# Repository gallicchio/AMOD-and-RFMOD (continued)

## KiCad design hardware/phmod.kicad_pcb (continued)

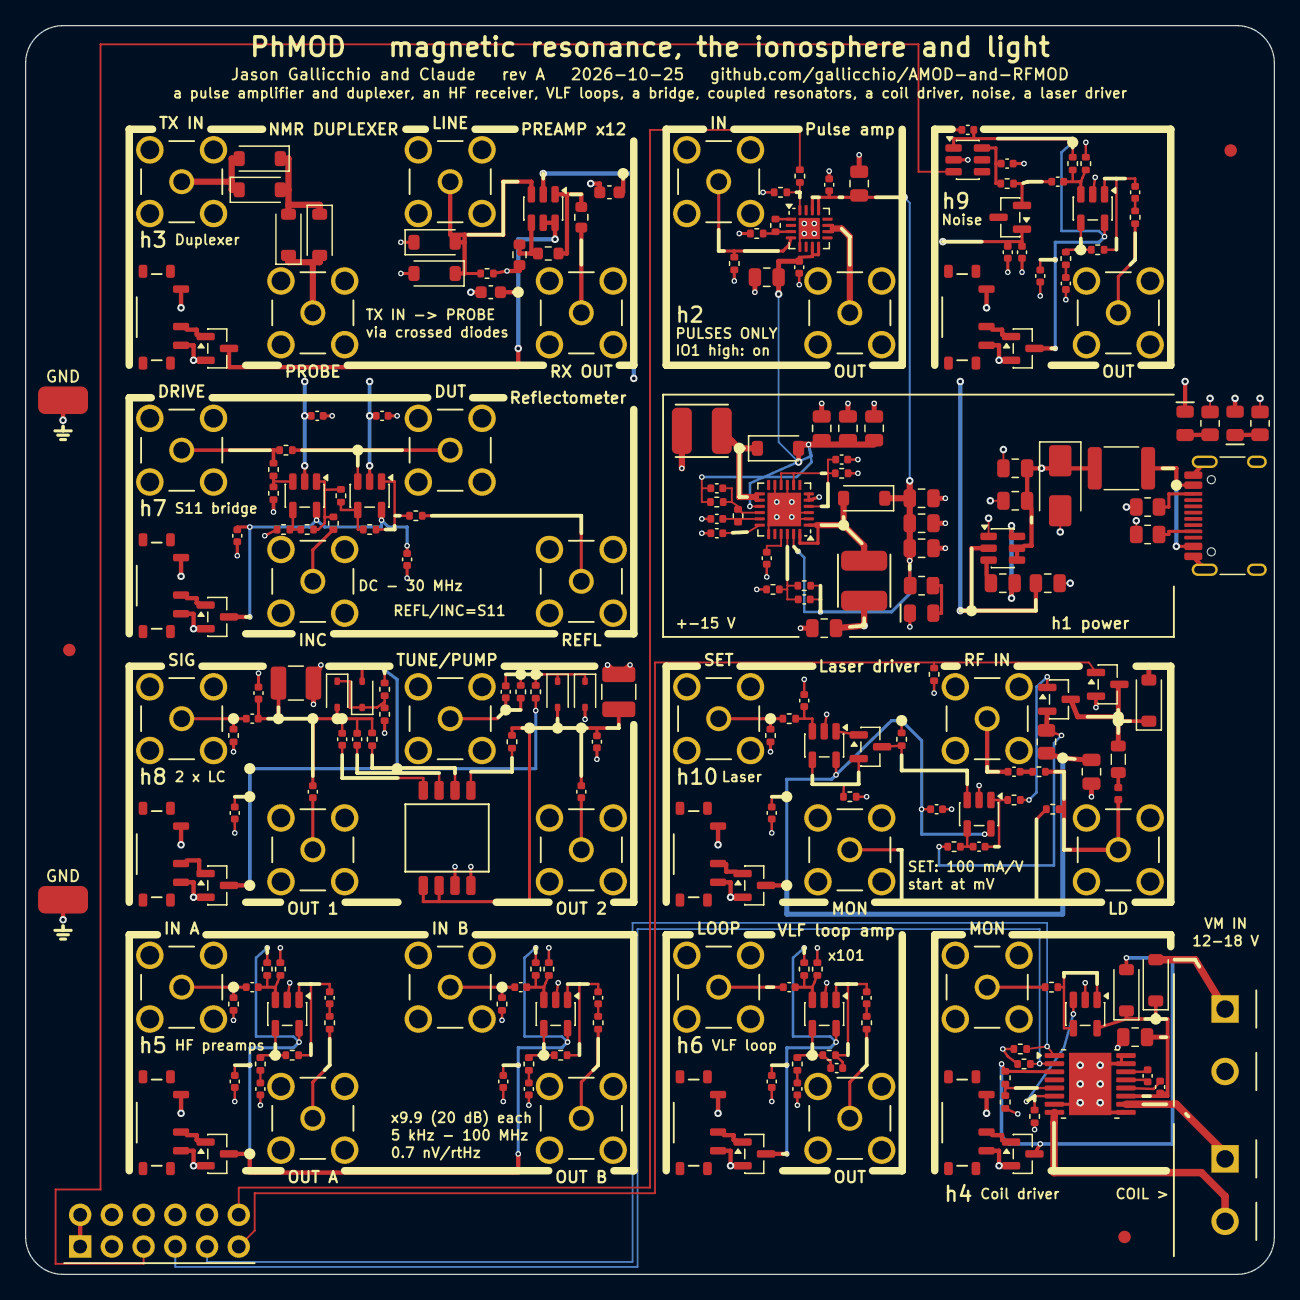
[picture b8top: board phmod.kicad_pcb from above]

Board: 4 copper layers, 100.0 x 100.0 mm, 234 parts (0 on the bottom side), 131 nets.

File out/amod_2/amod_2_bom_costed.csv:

Comment,Designator,Footprint,LCSC Part #,MPN,Qty,Unit $,Ext $,JLC
220n,C104,C_0402_1005Metric,C47129,CL05A224KA5NNNC,1,0.0083,0.008,extended
4.7n,C105,C_0402_1005Metric,C84705,CL05B472KB5NNNC,1,0.0044,0.004,extended
7.5p,C106,C_0402_1005Metric,C43514,0402CG7R5C500NT,1,0.0025,0.003,extended
4.7u,C108,C_0805_2012Metric,C1779,CL21A475KAQNNNE,1,0.0343,0.034,basic
22n,C402,C_0402_1005Metric,C337699,CL05B223KB5NNNC,1,0.0045,0.004,extended
4.7p,C802,C_0402_1005Metric,C1569,0402CG4R7C500NT,1,0.0058,0.006,extended
1p,C804,C_0402_1005Metric,C1550,0402CG1R0C500NT,1,0.0029,0.003,basic
1n,C806,C_0402_1005Metric,C1523,0402B102K500NT,1,0.0038,0.004,basic
6.8p,"C113,C807",C_0402_1005Metric,C1576,0402CG6R8C500NT,2,0.0026,0.005,extended
100n,"C301,C302",C_0603_1608Metric,C14663,CC0603KRX7R9BB104,2,0.0084,0.017,basic
10n,"C112,C1003",C_0402_1005Metric,C15195,CL05B103KB5NNNC,2,0.0039,0.008,basic
100p,"C603,C903,C1005",C_0402_1005Metric,C1546,0402CG101J500NT,3,0.0033,0.010,basic
2.2p,"C801,C803,C805,C808",C_0402_1005Metric,C1559,0402CG2R2C500NT,4,0.0037,0.015,extended
1u,"C501,C502,C503,C505,C506,C507,C601,C602,C604,C901,C905,C906,C907",C_0402_1005Metric,C14445,CL05A105KP5NNNC,13,0.0053,0.069,extended
10u,"C101,C102,C103,C109,C110,C111,C114,C115,C116,C117,C202,C204,C401,C1004",C_0805_2012Metric,C15850,CL21A106KAYNNNE,14,0.0426,0.596,basic
100n,"C107,C201,C203,C403,C504,C508,C605,C701,C702,C703,C704,C809,C902,C904,C908,C1001,C1002,C1006",C_0402_1005Metric,C1525,CL05B104KO5NNNC,18,0.0035,0.063,basic
SMAJ5.0A,D103,D_SMA,C78401,SMAJ5.0A,1,0.0537,0.054,extended
BB133,"D801,D802,D803,D804",D_SOD-323,C5334579,BB133,4,0.0604,0.242,extended
B5819W,"D101,D102,D401,D402,D1001",D_SOD-123,C64885,B5819W,5,0.0195,0.098,extended
1N4148W,"D301,D302,D303,D304,D305,D306",D_SOD-123,C81598,1N4148W,6,0.0124,0.074,basic
2A,F101,Fuse_1812_4532Metric,C210837,MF-MSMF200-2,1,0.0650,0.065,extended
USB-C,J101,USB_C_Receptacle_HRO_TYPE-C-31-M-12,C165948,TYPE-C-31-M-12,1,0.1888,0.189,extended
VM in,J402,TerminalBlock_KF301_1x02_P5.00mm,C474881,KF301-5.0-2P,1,0.1017,0.102,extended
coil,J403,TerminalBlock_KF301_1x02_P5.00mm,C474881,KF301-5.0-2P,1,0.1017,0.102,extended
Pmod,J505,PinHeader_2x06_P2.54mm_Horizontal_PZ254R-12-12P,C492434,PZ254R-12-12P,1,0.1036,0.104,extended
SMA,"J201,J202,J301,J302,J303,J304,J401,J501,J502,J503,J504,J601,J602,J701,J702,J703,J704,J801,J802,J803,J804,J901,J1001,J1002,J1003,J1004",SMA_BWSMA-KE-Z001_Vertical,C496549,BWSMA-KE-Z001,26,0.4043,10.512,extended
330n,L1001,L_0805_2012Metric,C98210,SDWL2012CR33JSTF,1,0.0851,0.085,extended
27n,L1002,L_0402_1005Metric,C882469,LQW15AN27NG80D,1,0.0902,0.090,extended
+15V,LED101,LED_0805_2012Metric_Kbar,C2296,KT-0805Y,1,0.0146,0.015,basic
-5V,LED102,LED_0805_2012Metric_Kbar,C84256,NCD0805R1,1,0.0135,0.013,basic
+5V,LED103,LED_0805_2012Metric_Kbar,C2297,KT-0805G,1,0.0164,0.016,basic
4.7u,"L101,L102",L_4x4_XRNR4030,C57269,SWPA4030S4R7MT,2,0.0603,0.121,extended
10u,"L801,L802",L_1210_3225Metric,C76835,NLV32T-100J-PF,2,0.0578,0.116,extended
MMBT3904,Q902,SOT-23,C20526,MMBT3904(RANGE:100-300),1,0.0116,0.012,basic
2N7002,Q1002,SOT-23,C8545,2N7002,1,0.0161,0.016,basic
AO3400A,Q1004,SOT-23,C20917,AO3400A,1,0.0889,0.089,basic
AO3401A,"Q301,Q401,Q501,Q601,Q701,Q801,Q901,Q1001,Q1003",SOT-23,C15127,AO3401A,9,0.0959,0.863,basic
105k,R101,R_0402_1005Metric,C25742,0402WGF1053TCE,1,0.0021,0.002,extended
1.3M,R102,R_0402_1005Metric,C423245,0402WGF1304TCE,1,0.0005,0.001,extended
88.7k,R104,R_0402_1005Metric,C25922,0402WGF8872TCE,1,0.0016,0.002,extended
1M,R105,R_0402_1005Metric,C26083,0402WGF1004TCE,1,0.0015,0.002,basic
4.7k,R106,R_0805_2012Metric,C17673,0805W8F4701T5E,1,0.0051,0.005,basic
698,R201,R_0402_1005Metric,C33359,0402WGF6980TCE,1,0.0010,0.001,extended
75,R202,R_0402_1005Metric,C25133,0402WGF750JTCE,1,0.0013,0.001,extended
4.7k,R205,R_0402_1005Metric,C25900,0402WGF4701TCE,1,0.0021,0.002,basic
1.1k,R302,R_0603_1608Metric,C22764,0603WAF1101T5E,1,0.0018,0.002,extended
49.9,R303,R_0603_1608Metric,C23185,0603WAF499JT5E,1,0.0021,0.002,basic
100R,R304,R_0603_1608Metric,C22775,0603WAF1000T5E,1,0.0023,0.002,basic
5.1k,R403,R_0402_1005Metric,C25905,0402WGF5101TCE,1,0.0023,0.002,basic
3.3k,R404,R_0402_1005Metric,C25890,0402WGF3301TCE,1,0.0036,0.004,basic
1.5k,R405,R_0402_1005Metric,C25867,0402WGF1501TCE,1,0.0029,0.003,basic
680,R901,R_0402_1005Metric,C25130,0402WGF6800TCE,1,0.0012,0.001,basic
10,R1007,R_0805_2012Metric,C17415,0805W8F100JT5E,1,0.0040,0.004,basic
47,R1008,R_0402_1005Metric,C25118,0402WGF470JTCE,1,0.0012,0.001,basic
5.1k,"R107,R108",R_0805_2012Metric,C27834,0805W8F5101T5E,2,0.0036,0.007,basic
1k,"R109,R110",R_0805_2012Metric,C17513,0805W8F1001T5E,2,0.0035,0.007,basic
2k,"R804,R807",R_0402_1005Metric,C4109,0402WGF2001TCE,2,0.0026,0.005,basic
240,"R504,R510,R904",R_0402_1005Metric,C25094,0402WGF2400TCE,3,0.0016,0.005,extended
27,"R505,R511,R905",R_0402_1005Metric,C25100,0402WGF270JTCE,3,0.0013,0.004,extended
100,"R103,R604,R1005",R_0402_1005Metric,C25076,0402WGF1000TCE,3,0.0012,0.004,basic
499,"R704,R705,R707,R708",R_0402_1005Metric,C4125,0402WGF4990TCE,4,0.0010,0.004,basic
1k,"R1002,R1003,R1004,R1006",R_0402_1005Metric,C11702,0402WGF1001TCE,4,0.0013,0.005,basic
10k,"R204,R502,R503,R508,R509,R603,R902,R903,R1009",R_0402_1005Metric,C25744,0402WGF1002TCE,9,0.0011,0.010,basic
100k,"R401,R402,R601,R602,R802,R803,R805,R806,R1010",R_0402_1005Metric,C25741,0402WGF1003TCE,9,0.0015,0.013,basic
49.9,"R203,R301,R406,R501,R506,R507,R512,R605,R701,R702,R703,R706,R709,R801,R906,R1001",R_0402_1005Metric,C25120,0402WGF499JTCE,16,0.0016,0.026,basic
DIP4,SW802,SW_DIP_SPSTx04_Slide_1.27mm_DSHP04,C40736,DSHP04TSGET,1,0.5450,0.545,extended
ON,"SW301,SW401,SW501,SW601,SW701,SW801,SW901,SW1001",SW_SPDT_Shouhan_MSK12C02,C431540,MSK12C02,8,0.0529,0.423,extended
GND,"TP9901,TP9902",TestPoint_Loop_RH-5019,C5199800,RH-5019,2,0.0966,0.193,extended
TPS65131,U101,QFN-24-1EP_4x4mm_P0.5mm_EP2.7x2.7mm,C87663,TPS65131RGER,1,2.8786,2.879,extended
LM2664,U102,SOT-23-6,C108573,LM2664M6X/NOPB,1,0.3346,0.335,extended
THS3491,U201,QFN-16-1EP_3x3mm_P0.5mm_EP1.7x1.7mm,C2058688,THS3491IRGTR,1,13.5355,13.536,extended
OPA847,U301,SOT-23-6,C160422,OPA847IDBVR,1,10.3296,10.330,extended
DRV8876,U401,HTSSOP-16-1EP_4.4x5mm_P0.65mm_EP3.4x5mm_Mask2.66x2.46mm,C575551,DRV8876PWPR,1,0.6612,0.661,extended
TPS22917,U901,SOT-23-6,C2681320,TPS22917DBVR,1,0.3653,0.365,extended
LMH6629,"U501,U502,U902",SOT-23-5,C2059678,LMH6629MFX/NOPB,3,5.4577,16.373,extended
OPA810,"U402,U601,U701,U702,U1001,U1002",SOT-23-5,C2833513,OPA810IDBVR,6,3.0996,18.598,extended

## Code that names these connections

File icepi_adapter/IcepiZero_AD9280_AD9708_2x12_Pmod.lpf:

# IcepiZero_AD9280_AD9708_2x12_Pmod
# HS-AD/DA V2.0 AD9280 ADC + AD9708 DAC, plus a Pmod
# GENERATED by make_boards.py from the same pin assignment as
# the PCB -- do not edit.  Rebuild with:
#     KICAD=10 ./kicad-python.sh make_boards.py

# ---- the converter module, through this adapter -------------
LOCATE COMP "ad0" SITE "R1";   # AD0, header pin 7 / GPIO4
IOBUF  PORT "ad0" IO_TYPE=LVCMOS33 PULLMODE=NONE DRIVE=4 SLEWRATE=SLOW;
LOCATE COMP "ad1" SITE "R3";   # AD1, header pin 11 / GPIO17
IOBUF  PORT "ad1" IO_TYPE=LVCMOS33 PULLMODE=NONE DRIVE=4 SLEWRATE=SLOW;
LOCATE COMP "ad2" SITE "N4";   # AD2, header pin 12 / GPIO18
IOBUF  PORT "ad2" IO_TYPE=LVCMOS33 PULLMODE=NONE DRIVE=4 SLEWRATE=SLOW;
LOCATE COMP "ad3" SITE "P3";   # AD3, header pin 13 / GPIO27
IOBUF  PORT "ad3" IO_TYPE=LVCMOS33 PULLMODE=NONE DRIVE=4 SLEWRATE=SLOW;
LOCATE COMP "ad4" SITE "P2";   # AD4, header pin 15 / GPIO22
IOBUF  PORT "ad4" IO_TYPE=LVCMOS33 PULLMODE=NONE DRIVE=4 SLEWRATE=SLOW;
LOCATE COMP "ad5" SITE "M2";   # AD5, header pin 16 / GPIO23
IOBUF  PORT "ad5" IO_TYPE=LVCMOS33 PULLMODE=NONE DRIVE=4 SLEWRATE=SLOW;
LOCATE COMP "ad6" SITE "L1";   # AD6, header pin 18 / GPIO24
IOBUF  PORT "ad6" IO_TYPE=LVCMOS33 PULLMODE=NONE DRIVE=4 SLEWRATE=SLOW;
LOCATE COMP "ad7" SITE "L2";   # AD7, header pin 19 / GPIO10
IOBUF  PORT "ad7" IO_TYPE=LVCMOS33 PULLMODE=NONE DRIVE=4 SLEWRATE=SLOW;
LOCATE COMP "aclk" SITE "J1";   # ACLK, header pin 21 / GPIO9
IOBUF  PORT "aclk" IO_TYPE=LVCMOS33 PULLMODE=NONE DRIVE=4 SLEWRATE=SLOW;
LOCATE COMP "dclk" SITE "G2";   # DCLK, header pin 23 / GPIO11
IOBUF  PORT "dclk" IO_TYPE=LVCMOS33 PULLMODE=NONE DRIVE=4 SLEWRATE=SLOW;
LOCATE COMP "da7" SITE "H2";   # DA7, header pin 24 / GPIO8
IOBUF  PORT "da7" IO_TYPE=LVCMOS33 PULLMODE=NONE DRIVE=4 SLEWRATE=SLOW;
LOCATE COMP "da6" SITE "G1";   # DA6, header pin 26 / GPIO7
IOBUF  PORT "da6" IO_TYPE=LVCMOS33 PULLMODE=NONE DRIVE=4 SLEWRATE=SLOW;
LOCATE COMP "da5" SITE "E1";   # DA5, header pin 29 / GPIO5
IOBUF  PORT "da5" IO_TYPE=LVCMOS33 PULLMODE=NONE DRIVE=4 SLEWRATE=SLOW;
LOCATE COMP "da4" SITE "F3";   # DA4, header pin 31 / GPIO6
IOBUF  PORT "da4" IO_TYPE=LVCMOS33 PULLMODE=NONE DRIVE=4 SLEWRATE=SLOW;
LOCATE COMP "da3" SITE "J3";   # DA3, header pin 32 / GPIO12
IOBUF  PORT "da3" IO_TYPE=LVCMOS33 PULLMODE=NONE DRIVE=4 SLEWRATE=SLOW;
LOCATE COMP "da2" SITE "E3";   # DA2, header pin 33 / GPIO13
IOBUF  PORT "da2" IO_TYPE=LVCMOS33 PULLMODE=NONE DRIVE=4 SLEWRATE=SLOW;
LOCATE COMP "da1" SITE "E4";   # DA1, header pin 35 / GPIO19
IOBUF  PORT "da1" IO_TYPE=LVCMOS33 PULLMODE=NONE DRIVE=4 SLEWRATE=SLOW;
LOCATE COMP "da0" SITE "D4";   # DA0, header pin 37 / GPIO26
IOBUF  PORT "da0" IO_TYPE=LVCMOS33 PULLMODE=NONE DRIVE=4 SLEWRATE=SLOW;

# ---- the Pmod socket J3: pmod[n-1] is the Pmod standard's IOn (pins 1-4, 7-10) -----
# ---- J3 layout: spec (make_boards.py PMOD_LAYOUT) -----
LOCATE COMP "pmod[0]" SITE "F2";   # PMOD1, socket pad 11, header pin 40 / GPIO21
IOBUF  PORT "pmod[0]" IO_TYPE=LVCMOS33 PULLMODE=NONE DRIVE=4 SLEWRATE=SLOW;
LOCATE COMP "pmod[1]" SITE "H3";   # PMOD2, socket pad 9, header pin 36 / GPIO16
IOBUF  PORT "pmod[1]" IO_TYPE=LVCMOS33 PULLMODE=NONE DRIVE=4 SLEWRATE=SLOW;
LOCATE COMP "pmod[2]" SITE "G3";   # PMOD3, socket pad 7, header pin 27 / GPIO0
IOBUF  PORT "pmod[2]" IO_TYPE=LVCMOS33 PULLMODE=NONE DRIVE=4 SLEWRATE=SLOW;
LOCATE COMP "pmod[3]" SITE "N1";   # PMOD4, socket pad 5, header pin 10 / GPIO15
IOBUF  PORT "pmod[3]" IO_TYPE=LVCMOS33 PULLMODE=NONE DRIVE=4 SLEWRATE=SLOW;
LOCATE COMP "pmod[4]" SITE "F1";   # PMOD5, socket pad 12, header pin 38 / GPIO20
IOBUF  PORT "pmod[4]" IO_TYPE=LVCMOS33 PULLMODE=NONE DRIVE=4 SLEWRATE=SLOW;
LOCATE COMP "pmod[5]" SITE "K3";   # PMOD6, socket pad 10, header pin 28 / GPIO1
IOBUF  PORT "pmod[5]" IO_TYPE=LVCMOS33 PULLMODE=NONE DRIVE=4 SLEWRATE=SLOW;
LOCATE COMP "pmod[6]" SITE "J2";   # PMOD7, socket pad 8, header pin 22 / GPIO25
IOBUF  PORT "pmod[6]" IO_TYPE=LVCMOS33 PULLMODE=NONE DRIVE=4 SLEWRATE=SLOW;
LOCATE COMP "pmod[7]" SITE "P1";   # PMOD8, socket pad 6, header pin 8 / GPIO14
IOBUF  PORT "pmod[7]" IO_TYPE=LVCMOS33 PULLMODE=NONE DRIVE=4 SLEWRATE=SLOW;

# ---- the Icepi Zero itself ----------------------------
LOCATE COMP "clk50" SITE "M1";   # 50 MHz oscillator -- the only clock on the board
IOBUF  PORT "clk50" IO_TYPE=LVCMOS33 PULLMODE=NONE;
LOCATE COMP "uart_tx" SITE "K15";   # to U9 (FT231X) RXD -> /dev/ttyUSB* on the host
IOBUF  PORT "uart_tx" IO_TYPE=LVCMOS33 PULLMODE=NONE;
LOCATE COMP "uart_rx" SITE "K16";   # from U9 (FT231X) TXD
IOBUF  PORT "uart_rx" IO_TYPE=LVCMOS33 PULLMODE=NONE;
LOCATE COMP "led0" SITE "E13";
IOBUF  PORT "led0" IO_TYPE=LVCMOS33 PULLMODE=NONE;
LOCATE COMP "led1" SITE "D14";
IOBUF  PORT "led1" IO_TYPE=LVCMOS33 PULLMODE=NONE;
LOCATE COMP "led2" SITE "E12";
IOBUF  PORT "led2" IO_TYPE=LVCMOS33 PULLMODE=NONE;
LOCATE COMP "led3" SITE "C13";
IOBUF  PORT "led3" IO_TYPE=LVCMOS33 PULLMODE=NONE;
LOCATE COMP "led4" SITE "D13";
IOBUF  PORT "led4" IO_TYPE=LVCMOS33 PULLMODE=NONE;
LOCATE COMP "btn0" SITE "C4";   # also the LiteX reset button
IOBUF  PORT "btn0" IO_TYPE=LVCMOS33 PULLMODE=UP;
LOCATE COMP "btn1" SITE "C5";
IOBUF  PORT "btn1" IO_TYPE=LVCMOS33 PULLMODE=UP;

# The oscillator, so nextpnr reports the real timing margin
# instead of guessing.
FREQUENCY PORT "clk50" 50 MHZ;

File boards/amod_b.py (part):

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    t.pwr_flags = [VMB]
    t.jack("BR", "I", "IJ", "out", "", silk="I 1V/A")
    bx = BUS_X - t.x0
    rsh = t.add("R", "R1206 0.1R", "0.1", 3.0, 3.25, 0, {"1": VM, "2": VMB}, label=None)
    t.via(VM, bx, BUS_END - t.y0)
    t.wire(VM, [(bx, BUS_END - t.y0), (rsh, "1")], width=WP)
    # VMB: a via beside the shunt, the back left to the gutter and down it to the driver
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    # slots to the left (to b7).  VDD's via is on the +3.3 V strip (the gutter between rows 1 and 2 runs under the middle)
    enc = t.add("U", "MT6701", "MT6701", cx, cy, 180, {"1": "+3V3", "3": "/ANG", "4": "GND", "6": "/ENC_DO", "7": "/PMOD4", "8": "/PMOD6"},
                hide_value=True, label=None)
    for net, pin, y in (("/ENC_DO", "6", cy - 0.635), ("/PMOD4", "7", cy + 0.635), ("/PMOD6", "8", cy + 1.905)):
        t.via(net, *ENC_VIA[net], fine=True)
        t.wire(net, [(enc, pin), ENC_VIA[net]], width=0.2)
    t.via("/ANG", *ENC_VIA["/ANG"], fine=True)
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    # the index sensor under the rim toward b9: its LED from +5 V through 180 ohm; collector and emitter on vias for b9
    a = math.radians(-60.0)
    qx, qy = cx + GIMBAL_R_INDEX * math.cos(a), cy + GIMBAL_R_INDEX * math.sin(a)
    q = t.add("U", "QRE1113GR", "QRE1113", qx, qy, 0, {"1": "QLA", "2": "GND", "3": "/IDX_C", "4": "/IDX_E"}, hide_value=True, label=None)
    rq = t.add("R", "R0805 180R", "180", qx - 0.9, qy - 4.86, 0, {"1": "+5V", "2": "QLA"}, label=None)
    t.wire("QLA", [(rq, "2"), (qx, qy - 3.6), (qx - 0.9, qy - 2.83), (q, "1")], width=W)
    t.via("+5V", qx - 3.0, qy - 4.86)
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    t.via(VMB, bx, 10.6)
    t.wire(VMB, [(drv, "8"), (23.2, Y + 0.67), (23.8, 10.27), (23.8, 10.6)], width=0.25)
    t.wire(VMB, [(23.8, 10.6), (bx, 10.6)], width=1.0)
    cvm = t.add("C", "C0402 100nF", "100n", 25.2, 12.0, 90, {"1": "GND", "2": VMB}, label=None)            # pad 2 up
    t.wire(VMB, [(cvm, "2"), (25.2, 10.9)], width=0.4)
    t.gnd_stub(cvm, "1", (26.2, 12.8), sym=(0, 0), width=W)
    cbk = t.add("C", "C0805 10uF", "10u", 28.4, 13.0, 0, {"1": "GND", "2": VMB}, label=None)
    t.wire(VMB, [(cbk, "2"), (29.35, 10.9)], width=0.6)
    t.gnd_stub(cbk, "1", (27.45, 14.4), sym=(0, 0), width=W)
    ccp = t.add("C", "C0402 100nF", "100n", 23.0, 11.9, 0, {"1": "CP", "2": VMB}, label=None)
    t.wire("CP", [(drv, "6"), (X + 0.8, 11.2), (ccp, "1")], width=F)
    t.wire(VMB, [(ccp, "2"), (23.8, 11.3), (23.8, 10.6)], width=0.25)
    # ---- EN: the three INL pins joined over the driver's top-left corner, from the comparator
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    low side only, sampled) it shows what a low-side amplifier misses."""
    t = Tile("b11", "phase current", [(3, 3)], supply="+-5 V", subtitle="INA240", sections=["Motors"])
    t.jack("BR", "IPA", "IJ", "out", "", silk="IPA 1V/A")
    rsh = t.add("R", "R1206 0.05R", "0.05", 3.6, 8.87, 0, {"1": "/PHA", "2": "/PHAM"}, label=None)
    t.wire("/PHA", [(-0.75, 8.87), (rsh, "1")], width=0.6)
    # the return to the terminal's pin 3, up and left along y 4.35
    t.wire("/PHAM", [(rsh, "2"), (5.6, 7.6), (5.6, 4.35), (-4.8, 4.35)], width=0.6)
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    t.fine = True
    F = 0.15
    imu = t.add("U", "LSM6DSO", "LSM6DSO", 10.5, 15.0, 270, {"1": "/PMOD3", "2": "GND", "3": "GND", "5": "+3V3", "6": "GND", "7": "GND", "8": "+3V3",
                                                             "12": "/PMOD8", "13": "/PMOD4", "14": "/PMOD7"}, hide_value=False, label=None)
    # SPI: the right side's three to vias staggered so the lanes on the back pass between them; MISO's from the top
    for net, pad, mid, via in (("/PMOD7", "14", [], (12.45, 14.5)), ("/PMOD8", "12", [], B6_VIA["/PMOD8"]), ("/PMOD4", "13", [], B6_VIA["/PMOD4"]),
                               ("/PMOD3", "1", [(11.25, 13.5)], (12.45, 13.5))):
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    through 49.9 ohm.  A white mark on the bell's rim gives a pulse once a turn: an index for the encoder, a tachometer."""
    t = Tile("b9", "index", [(2, 0)], supply="+-5 V", subtitle="QRE1113", sections=["Motors"])
    t.jack("BR", "IDX", "XJ", "out", "")
    ud = t.add("U", "OPA810", "OPA810", 10.6, 9.0, 0, {"1": "XO", "2": "-5V", "3": "GND", "4": "/IDX_C", "5": "+5V"}, hide_value=False, label=None)
    rf = t.add("R", "R0402 4.7k", "4.7k", 10.6, 12.0, 0, {"1": "/IDX_C", "2": "XO"}, label=None)
    cf = t.add("C", "C0402 100pF", "100p", 10.6, 13.2, 0, {"1": "/IDX_C", "2": "XO"}, label=None)
    re = t.add("R", "R0402 100R", "100", 6.0, 16.4, 0, {"1": "/IDX_E", "2": "-5V"}, label=None)
    ro = t.add("R", "R0402 49.9R", "49.9", 15.25, 10.6, 90, {"1": "XJ", "2": "XO"}, label=None)
    for (net, a, b) in (("/IDX_C", (rf, "1"), (ud, "4")), ("/IDX_C", (cf, "1"), (rf, "1")), ("XO", (rf, "2"), (ud, "1")), ("XO", (cf, "2"), (rf, "2")),
                        ("XO", (ro, "2"), (ud, "1"))):
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
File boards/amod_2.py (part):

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    t.wire("-15V", [(cn2, "2"), (9.55, 13.75)], width=0.4)
    # PD: 4.7 k from Pmod IO1 (along the top from the gutter on the left), 10 k to ground
    rpd = t.add("R", "R0402 10k", "10k", 9.7, 5.6, 0, {"1": "GND", "2": "PD"}, label=None)
    rs = t.add("R", "R0402 4.7k", "4.7k", 11.25, 4.3, 90, {"1": "PD", "2": "/PMOD1"}, label=None)              # pad 1 down
    t.wire("PD", [(u, "16"), (11.25, 5.6), (rpd, "2")], width=F)
    t.wire("PD", [(11.25, 5.6), (rs, "1")], width=F)
    gnd(t, rpd, "1", (8.3, 5.6), w=0.2)
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    used = PMOD_USED                                       # the lines some tile uses; the others stay open on the plug
    pads = {"12": "/PMOD1", "10": "/PMOD2", "8": "/PMOD3", "6": "/PMOD4", "11": "/PMOD5", "9": "/PMOD6", "7": "/PMOD7", "5": "/PMOD8"}
    pins = {k: v for k, v in pads.items() if v in used}
    pins.update({"3": "GND", "4": "GND", "1": "/PMOD_VCC", "2": "/PMOD_VCC"})
    pm = t.add("J", "PMOD", "Pmod", 2.97, 24.25, 0, pins, hide_value=True)
    t.wire("/PMOD_VCC", [(pm, "1"), (pm, "2")], silk=False)
    t.text(1.2, 9.4, "Y5", 1.2, 0.2, "left")
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    power_header(t, rail="+5V")
    t.wire("VS", [HDR_VS, (10.2, 18.1)], width=0.35)
    # the switch: TPS22917 (rot 0: VIN 1, GND 2, ON 3 down the left; VOUT 6 top-right; CT and QOD open); ON is Pmod IO8
    sw = t.add("U", "TPS22917", "TPS22917", 3.2, 3.0, 0, {"1": "VS", "2": "GND", "3": "/PMOD8", "6": "VN"}, hide_value=False, label=None)
    t.gnd_stub(sw, "2", (3.2, 3.0), sym=(0, 0), width=0.25, fine=True)
    cvs = t.add("C", "C0402 1uF", "1u", 3.2, 0.6, 180, {"1": "VS", "2": "GND"}, label=None)                  # rot 180: VS pad right
    gnd(t, cvs, "2", (1.6, 0.6), w=0.25)
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    # U1: INC = 2 B.  rot 270: +IN (13.65, 7.26), V- (14.6, 7.26), OUT (15.55, 7.26); -IN (13.65, 9.54), V+ (15.55, 9.54)
    u1 = t.add("U", "OPA810", "OPA810", 14.6, 8.4, 270, {"1": "O1", "2": "-5V", "3": "B", "4": "N1", "5": "VS"}, hide_value=False, label=None)
    t.wire("B", [(12.1, 7.25), (u1, "3")], width=0.2)
    rf1 = t.add("R", "R0402 499R", "499", 14.8, 11.1, 0, {"1": "N1", "2": "O1"}, label=None)
    rg1 = t.add("R", "R0402 499R", "499", 12.9, 11.1, 0, {"1": "GND", "2": "N1"}, label=None)
    t.wire("N1", [(u1, "4"), (13.65, 11.1)], width=0.2)
    t.wire("N1", [(rg1, "2"), (rf1, "1")], width=0.2)
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    rg2 = t.add("R", "R0402 499R", "499", 17.5, 8.4, 270, {"1": "O1", "2": "N2"}, label=None)                  # pad 1 up
    t.wire("O1", [(16.2, 7.92), (rg2, "1")], width=0.2)
    t.wire("N2", [(rg2, "2"), (17.5, 9.54), (u2, "4")], width=0.2)
    rf2 = t.add("R", "R0402 499R", "499", 19.8, 11.1, 0, {"1": "N2", "2": "O2"}, label=None)
    t.wire("N2", [(u2, "4"), (18.85, 11.1), (rf2, "1")], width=0.2)
    ro2 = t.add("R", "R0402 49.9R", "49.9", 23.5, 10.0, 0, {"1": "O2", "2": "REFL"}, label=None)
    t.wire("O2", [(u2, "1"), (21.8, 7.26), (21.8, 10.0), (ro2, "1")], width=0.2)
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    cbulk = t.add("C", "C0805 10uF", "10u", 34.6, 9.0, 90, {"1": "GND", "2": "VS"}, label=None)                 # rot 90: pad 2 up
    t.wire("VS", [(32.3, 7.9), (34.6, 8.0875)], width=0.4)
    gnd(t, cbulk, "1", (34.6, 11.0), w=0.4)
    q3 = t.add("Q", "NFET", "AO3400A", 35.9, 2.0, 0, {"1": "/PMOD5", "2": "GND", "3": "ID"}, hide_value=False, label=None)
    gnd(t, q3, "2", (34.9625, 3.85), w=0.3)
    t.wire("ID", [(q2, "3"), (33.5, 4.6), (36.75, 4.6), (36.75, 2.0), (q3, "3")], width=0.4)
    la = t.add("L", "L0805 330nH", "330n", 36.75, 8.0, 270, {"1": "ID", "2": "LM"}, label=None)                 # pad 1 up
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    t.wire("MON", [(rmon, "1"), (30.2, 12.8), (30.2, 19.6), (19.4, 19.6), (19.4, 15.25), (jmon, "1")], width=0.25)
    # ---- IO5 along the top to the shunt's gate, 100 k holding it low
    t.wire("/PMOD5", [(-0.35, 0.25), (34.4, 0.25), (q3, "1")], width=F, silk=False)
    rsd = t.add("R", "R0402 100k", "100k", 22.0, 1.2, 270, {"1": "/PMOD5", "2": "GND"}, label=None)
    t.wire("/PMOD5", [(22.0, 0.25), (rsd, "1")], width=F)
    gnd(t, rsd, "2", (22.0, 2.7), w=0.2)
    # ---- VS on the back: the switch's drain up x 10.2 to U1; on to REF's 1 k, U2 and a 100 nF; along the gutter to the 10 ohm
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    t.wire("/PMOD6", [(9.55, 9.5), (u, "1")], width=F)
    t.via("/PMOD7", 8.95, 10.875, fine=True)
    t.wire("/PMOD7", [(8.95, 10.875), (u, "2")], width=F)
    rpd6 = t.add("R", "R0402 100k", "100k", 7.4, 9.7, 0, {"1": "GND", "2": "/PMOD6"}, label=None)
    t.wire("/PMOD6", [(rpd6, "2"), (9.55, 9.5)], width=F)
    rpd7 = t.add("R", "R0402 100k", "100k", 7.7, 10.9, 0, {"1": "GND", "2": "/PMOD7"}, label=None)
    t.wire("/PMOD7", [(rpd7, "2"), (8.95, 10.875)], width=F)
    gnd(t, rpd6, "1", (6.0, 9.7), w=0.2)
    t.wire("GND", [(rpd7, "1"), (6.4, 10.3), (6.0, 9.7)], width=0.2, silk=False)
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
